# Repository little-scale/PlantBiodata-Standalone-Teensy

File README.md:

Standalone Audio / Modular setup that makes use of the wonderful work done over here by Sam Cusumano / electricity for progress: https://github.com/electricityforprogress/BiodataFeather

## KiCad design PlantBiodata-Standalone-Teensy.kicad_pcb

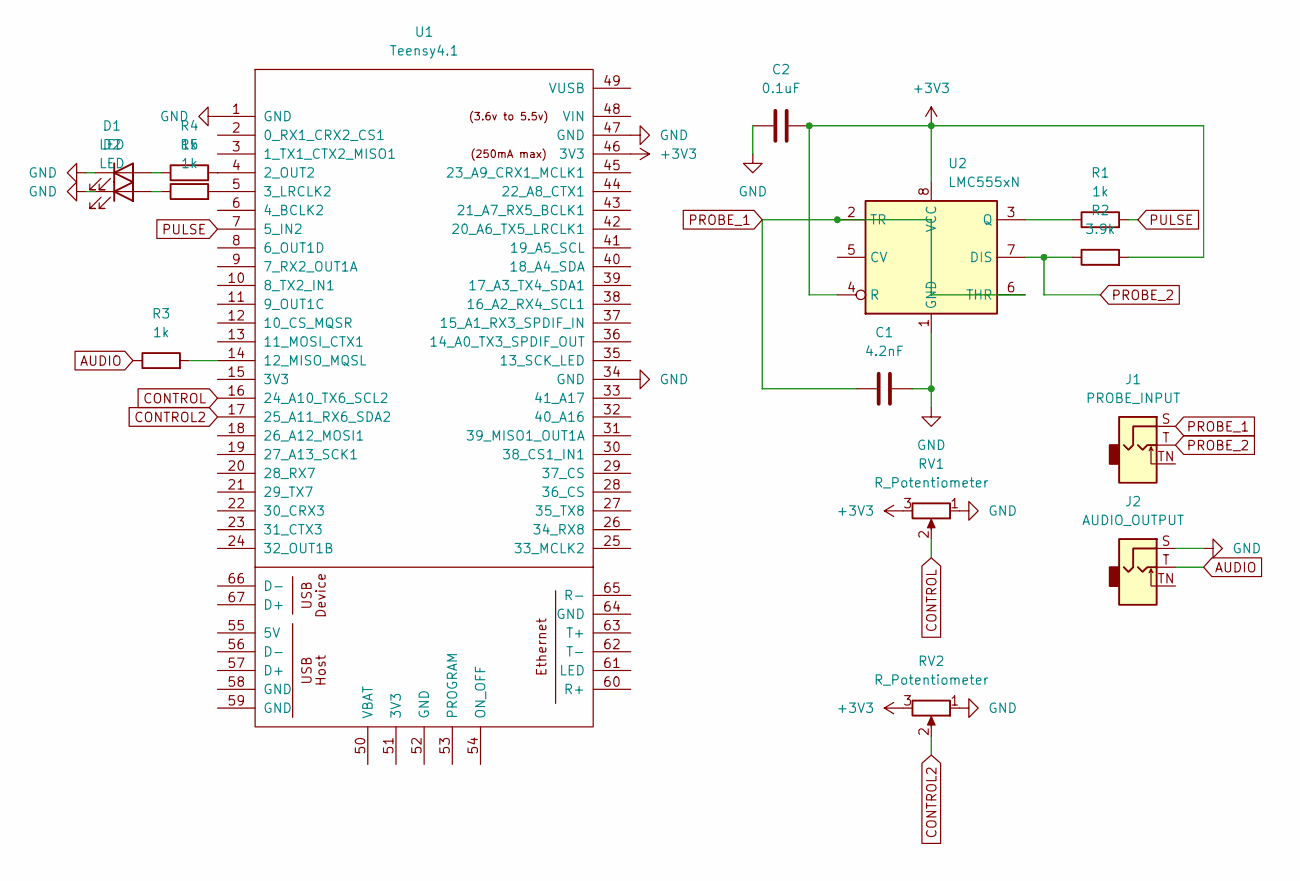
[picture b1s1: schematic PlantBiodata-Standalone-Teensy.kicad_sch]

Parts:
C1: 4.2nF; C_Disc_D3.0mm_W2.0mm_P2.50mm
C2: 0.1uF; C_Disc_D3.0mm_W2.0mm_P2.50mm
D1, D2: LED; LED_D3.0mm
J1: PROBE_INPUT; Jack_3.5mm_QingPu_WQP-PJ398SM_Vertical_CircularHoles
J2: AUDIO_OUTPUT; Jack_3.5mm_QingPu_WQP-PJ398SM_Vertical_CircularHoles
R1, R3, R4, R5: 1k; R_Axial_DIN0204_L3.6mm_D1.6mm_P7.62mm_Horizontal
R2: 3.9k; R_Axial_DIN0204_L3.6mm_D1.6mm_P7.62mm_Horizontal
RV1, RV2: R_Potentiometer; Potentiometer_Alpha_RD901F-40-00D_Single_Vertical
U1: Teensy4.1; Teensy41
U2: LMC555xN; DIP-8_W7.62mm_Socket

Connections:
+3V3: C2.2, R2.2, RV1.3, RV2.3, U1.46 (3V3), U2.4 (R), U2.8 (VCC)
AUDIO: J2.T, R3.1
CONTROL: RV1.2, U1.16 (24_A10_TX6_SCL2)
CONTROL2: RV2.2, U1.17 (25_A11_RX6_SDA2)
GND: C1.2, C2.1, D1.1 (K), D2.1 (K), J2.S, RV1.1, RV2.1, U1.1 (GND), U1.34 (GND), U1.47 (GND), U2.1 (GND)
unnamed: D1.2 (A), R4.1
unnamed: D2.2 (A), R5.1
unnamed: R4.2, U1.4 (2_OUT2)
unnamed: R5.2, U1.5 (3_LRCLK2)
unnamed: R3.2, U1.14 (12_MISO_MQSL)
unnamed: R1.1, U2.3 (Q)
PROBE_1: C1.1, J1.S, U2.2 (TR), U2.6 (THR)
PROBE_2: J1.T, R2.1, U2.7 (DIS)
PULSE: R1.2, U1.7 (5_IN2)

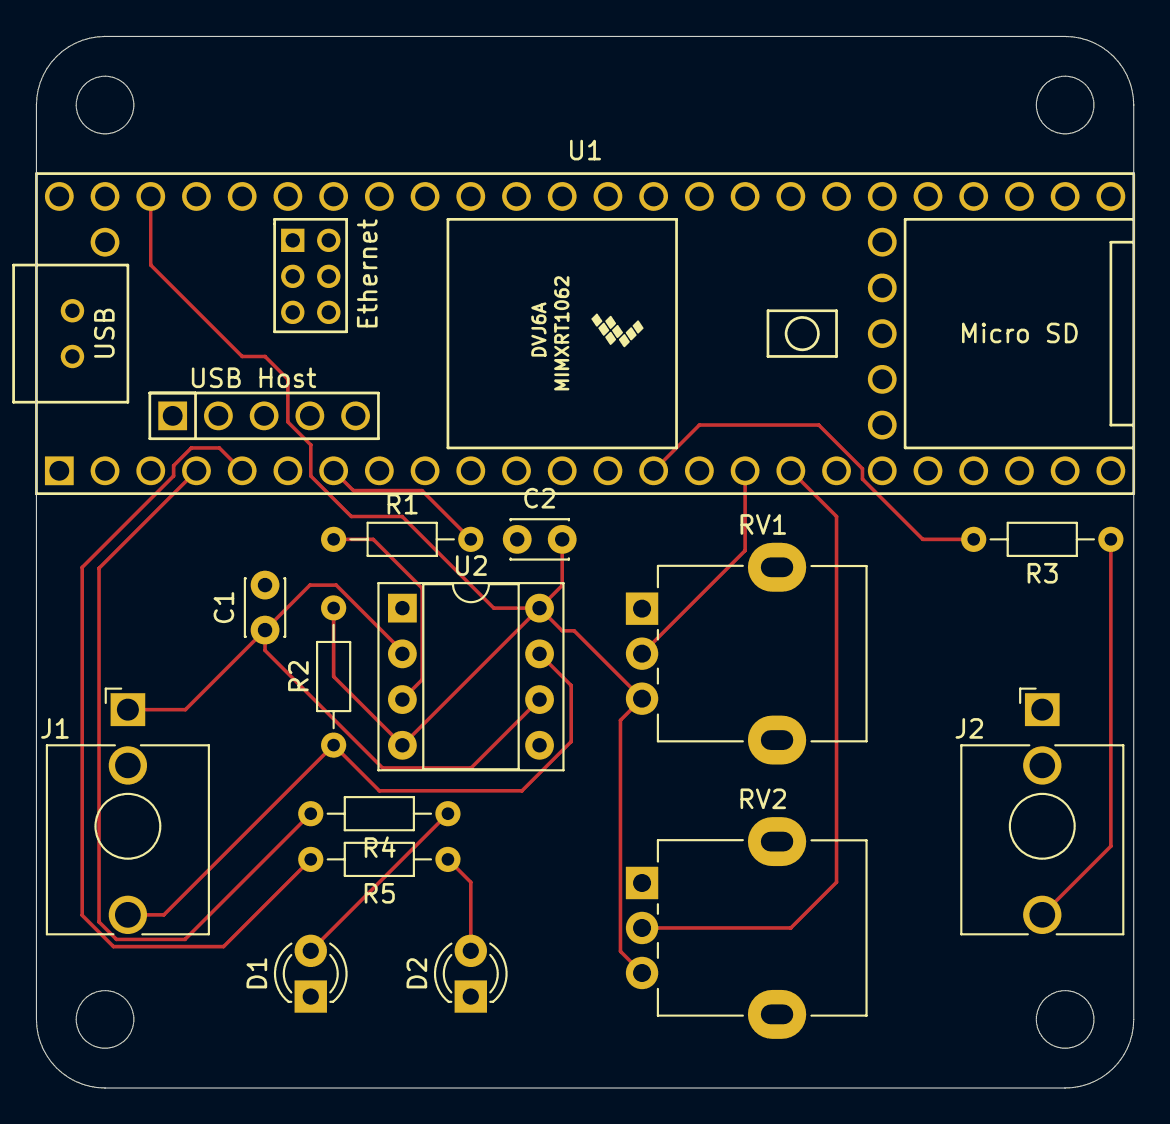
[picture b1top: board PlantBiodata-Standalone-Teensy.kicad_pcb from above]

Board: 2 copper layers, 61.0 x 58.4 mm, 15 parts (0 on the bottom side), 14 nets.

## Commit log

2025-02-19 Rename TeensyPlant.kicad_pcb to PlantBiodata-Standalone-Teensy.kicad_pcb
2025-02-19 Rename Plant Teensy Box - Box.stl to PlantBiodata-Standalone-Teensy - Box.stl
2025-02-19 Rename Plant Teensy Box - Lid A.stl to PlantBiodata-Standalone-Teensy - Lid A.stl
2025-02-19 Rename Plant Teensy Box - Lid B.stl to PlantBiodata-Standalone-Teensy - Lid B.stl
2025-02-19 Rename TeensyPlant.kicad_sch to PlantBiodata-Standalone-Teensy.kicad_sch
2025-02-19 Rename Teensy_Plant_Standalone_Audio.ino to PlantBiodata-Standalone-Teensy_Audio.ino
